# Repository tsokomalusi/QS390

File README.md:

# QS390
This PCB design project was developed by following an interactive stream led by Petr Dvorak[Petr Dvorak] (https://www.youtube.com/@hwidvorakinfo) .
It is not intended for financial gain,rather it serves as a learning opportunity aimed at improving my skills in PCB design. This experince proved to be valuable, as it
provided insight into symbol creation and the image converter Kicad feature, while also requiring adjustments during the routing process.

Software Tools used:
- CAD Software: Kicad
- VCS (Version Control System): Git and GitBash
- Online Server: Github
- Fabricator: JLCPCB

## PCB Layout (2-Layer Design)

## 3D Overview
### Top View

### Bottom View

## JLCPCB Gerber Viewer

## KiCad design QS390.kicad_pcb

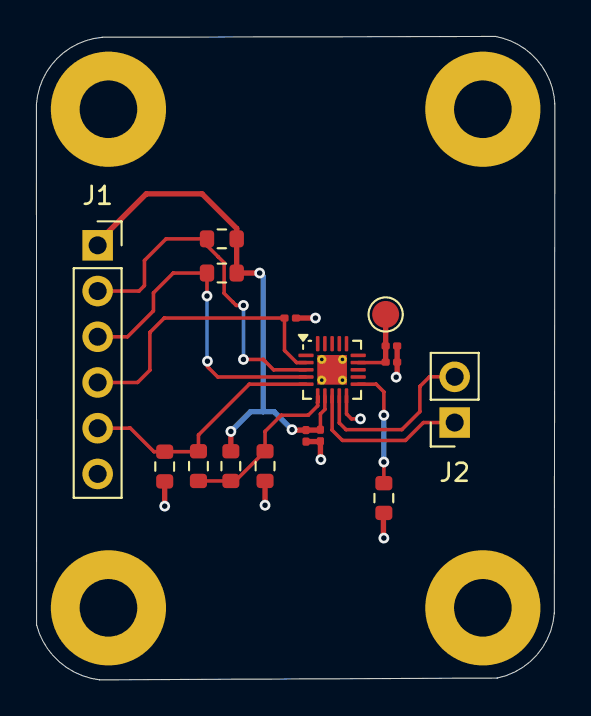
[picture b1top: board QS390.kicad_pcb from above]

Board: 2 copper layers, 28.8 x 35.7 mm, 20 parts (0 on the bottom side), 11 nets.

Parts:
C1: 100n_25V; C_0201_0603Metric
C2, C4: 100p; C_0201_0603Metric
C3: 10u_10V; C_0201_0603Metric
C5: 4u7_16V; C_0201_0603Metric
H1, H2, H3, H4: M3.2_Pad; MountingHole_3.2mm_M3_Pad
J1: Conn_01x06; PinSocket_1x06_P2.54mm_Vertical
J2: Conn_01x02; PinSocket_1x02_P2.54mm_Vertical
R1, R3: 3K3; R_0603_1608Metric
R2, R4, R7: 0R; R_0603_1608Metric
R5, R6: 4K7; R_0603_1608Metric
TP1: VREG; TestPoint_Pad_D1.5mm
U1: IQS390; QFN-20-1EP_3x3mm_P0.4mm_EP1.65x1.65mm_ThermalVias

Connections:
+3V3: C2.1, C3.1, J1.1, R1.1, R3.1, R5.1, U1.7 (VDD)
/ADDR-PWM: J1.5, R2.1, R4.1, U1.5 (ADDR_SEL/PWM_IN)
/MCLR: C1.1, J1.4, U1.2 (MCLR)
/SCL: J1.3, R3.2, U1.4 (SCL/DIR)
/SDA: J1.2, R1.2, U1.3 (SDA/NC)
GND: C1.2, C2.2, C3.2, C4.2, C5.2, H1.1, H2.1, H3.1, H4.1, J1.6, R2.2, R6.2, R7.2, U1.10 (VSS), U1.21 (EP)
unnamed: J2.1, U1.8 (M+)
unnamed: J2.2, U1.9 (M-)
unnamed: R7.1, U1.11 (MODE_SEL)
unnamed: R4.2, R5.2, R6.1, U1.6 (TRIG_HAPTICS/AUTO_WAKE)
unnamed: C4.1, C5.1, TP1.1, U1.14 (VREG)

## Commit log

2025-02-27 uploading QS390 PCB project
